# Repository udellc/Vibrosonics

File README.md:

# Vibrosonics

## Experience audio through vibration

**Vibrosonics** is a real-time audio-to-haptics system with an interactive web interface that allows deaf, hard-of-hearing, and sensory-focused users feel sound through vibrarions.

[**Documentation (Doxygen)**](https://udellc.github.io/Vibrosonics/) \
**Hardware:** Adafruit ESP32 Feather, MAX9744 Amplifier board, TT25-8 puck
transducer, 3.5mm audio jack cable \
**Dependencies:** [AudioLab](https://github.com/synytsim/AudioLab)
· [AudioPrism](https://github.com/udellc/AudioPrism)
· [Fast4ier](https://github.com/jmerc77/Fast4ier)

## Table of Contents

- [Why Vibrosonics Matters](#why-vibrosonics-matters)
- [Key Features](#key-features)
- [Arduino Setup](#arduino-setup)
- [Web Development Setup](#web-development-setup)
- [ESP32 Web Server Setup](#esp32-web-server-setup)
- [Developer Notes](#developer-notes)
- [Contributors](#contributors)

## Why Vibrosonics Matters

Millions of people experience barriers when it comes to audio-based media such as music, games, alerts, or live events. Vibrosoncis transforms those experiences by converting sound into meaningful tactile feedback.

Instead of hearing a beat, you **feel it**.

Built in collaboration with **[Cymaspace](https://www.cymaspace.org/)**, an organization whose goal is to make culture and arts accessible for the deaf and hard-of-hearing community, Vibrosonics is designed to make music, entertainment, and environments more inclusive while also opening up new immersive experiences for everyone. This group makes up our primary audience, as haptic feedback can be used to replace or enhance audio. Some secondary users would be employers whose work environments make pure audio based communication difficult. They could instead receive important audio cues through haptics.

## Key Features

**Real-Time Audio Conversion**
Transforms live audio input directly into haptic vibration with minimal latency.

**Configurable Settings Through Web Application**
A browser-based app allows users to adjust haptic feedback in real-time with no recompiling or device flashing required.

**Frequency-Aware Feedback**
Different pitches and intensities map to distinct vibration patterns, preserving musical structure and adding depth.

**Accessible by Design**
Built specifically for deaf and hard-of-hearing users, while also enhancing experiences for others.

_[View the most stable version on GitHub](https://github.com/udellc/Vibrosonics/tree/main)_

## Arduino Setup

### 1. Install Arduino IDE and ESP32 Board Support

- Download [Arduino IDE](https://www.arduino.cc/en/software/)
- Go to **Tools > Boards > Boards Manager**
- Search and install `esp32` by **Espressif Systems**

### 2. Set Board and Ports

- Plug in the board (you may need to install USB drivers)
- Go to the top drop down menu and click `Select other board and port...`
- In the pop up window, search for `Adafruit ESP32 Feather` and select it along
with `COMX` for port where `X` is a number 0-6
  - You may need to download a driver to see the port ([Windows
    Tutorial](https://randomnerdtutorials.com/install-esp32-esp8266-usb-drivers-cp210x-windows/))
  - On Linux, this is the `ch341` driver

### 3. Add Libraries

Navigate to the Arduino libraries folder. This is usually located in
`Documents/Arduino/libraries/` for Windows and `~/Arduino/libraries/` for Mac and Linux.

Clone the repositories into the libraries folder:

```bash
cd "/path/to/Arduino/libraries/"
git clone https://github.com/synytsim/AudioLab.git
git clone https://github.com/udellc/AudioPrism.git
git clone https://github.com/jmerc77/Fast4ier.git
```

Verify that the libraries are installed by opening Arduino IDE and going to
**Sketch > Include Library > Manage Libraries...**. You should see `AudioLab`,
`AudioPrism`, and `Fast4ier` in the list.

### 4. Upload a Sketch

You should be ready to use the example sketches or create your own! To upload a
sketch to the Vibrosonics hardware:

- Plug in the ESP32 via USB
- Open your own sketch or one of our examples from **File > Examples >
Vibrosonics > \[Example Name]**
- Press the upload (➜) in the top left to compile and upload your sketch

## Web Development Setup

### 1. Install Node.js and npm

- Download and install Node.js through your prefered web browser. This will also install npm.

### 2. Install Dependencies

- Open a terminal and navigate to the `WebApp/` directory of the repository.

- Run the following command to install the required dependencies:

```bash
npm install
```

### 3. Start the Development Server

- Run the following command to start the development server:

```bash
# This will start the server and provide a local URL at localhost. Once the server is running,
npm run dev

# Opens the application in your default web browser.
o

# Manually restarts the server
r

# Stops the server
q
```

### 4. Additional Commands

**Production Build:**
To build the application for production, run:

```bash
# This will produce optimized files in the `dist/` directory
npm run build

# This will preview the production build locally
npm run preview
```

**Run Linter Tool:**
To run ESLint for .js and .jsx files, run:

```bash
# This will scan the target files for any syntax issues or potential bugs
npm run lint

# This will automatically fix any fixable issues found by ESLint
npm run lint.fix
```

### 5. Troubleshooting

If you encounter any issues during setup or development, consider the following steps:

- Ensure that Node.js and npm are correctly installed by running `node -v` and `npm -v` in your terminal.
- Check for any error messages in the terminal and refer to the documentation of the specific tools or libraries being used.
- Make sure all dependencies are installed correctly by running `npm ci` for a clean install. If issues still persist, try deleting the `node_modules/` directory and running `npm install` again.

## ESP32 Web Server Setup

**SD File System Setup:**
To deploy the WiFi web app onto the ESP32, we'll need to store the web app onto a micro SD card connected to the ESP32. View `WebApp/main/fileSys.h` for the pin connections, these directions assume that the pins are connected properly.

**Note:** Uploading the web app onto the SD card only needs to be done everytime a new build of the web app is needed.

### 1. Setup Upload Mode (Necessary if web app is not on the ESP32, otherwise skip)

- Navigate to the `WebApp/main/config.h` file and uncomment the following line to setup the ESP32 in upload mode

```cpp
#define DEV_MODE_EN
```

- Build and upload `main.ino` in the ArduinoIDE once connected to a COM port.
- Connect to the Wi-Fi access point on your device, name of the network is **Vibrosonics-Dev**.
- Open a web browser and open `http://vibrosonics/dev`.
- Enter the directory you want to write to and select the file to upload.
- Click the upload button to write the file. **Note:** Open the Serial monitor in ArduinoIDE to view the files on the SD card.
- Once successful, exit the web app, comment out the `DEV_MODE_EN` macro and rebuild and upload `main.ino`.

### 2. Connect to the Web App

- Connect to the Wi-Fi access point on your device, name of the network is **Vibrosonics-Unsecure**.
- Open a web browser and navigate to `http://vibrosonics`.
- Follow the directions provided by the web app

## Developer Notes

### Library Architecture

The Vibrosonics library aims to streamline three processes to enable
translating audio into the haptic range: audio signal processing, audio
analysis and finally audio synthesis. We utilize a few libraries to achieve
this.

The first is AudioLab, which handles the audio signals between the external
hardware and the processor. It reads audio from the analog-to-digital
converters (ADC) and writes signals to the digital-to-analog converters (DAC)
for synthesis. The captured audio signals from the ADC are analyzed using the
other two library dependencies.

Fast4ier is used to perform the Fast Fourier Transform (FFT) on the signal
data, which converts it from a representation of the signal over time (time
domain) to a representation of how the signal is distributed over a range of
frequency bands (frequency domain). The bandwidth of the frequency domain, or
the max frequency, is equal to half of the sample rate of the ADC. Similarly,
the number of different frequency bands is equal to half of the window size of
the ADC.

AudioPrism is a library which analyzes the frequency domain data using various
algorithms. By filtering this data for different AudioPrism analysis modules,
we can detect certain elements of the audio signal. With music, this allows us
to detect percussion, isolate prominent vocals and melodies, and more. With
this analysis, distinct vibrations can be made to model elements of music by
re-synthesizing these findings through AudioLab translated down into the haptic
frequency range (0-230Hz).

### Web App Architecture

The VibroSonics application utilizes both cores on the ESP32 for efficient real-time audio processing and web-based configuration.

#### System Overview

- **Core 0**: Handles the web server and HTTP request processing
- **Core 1**: Runs the real-time audio analysis and haptic synthesis loop

#### Architecture Components

##### Frontend (Web App)

- **Framework**: React/Preact application built with Vite
- **Location**: Served from SD card on ESP32
- **Access**: Available at `http://vibrosonics` when connected to the device's WiFi AP
- **Pages**: 
  - Landing page for global settings
  - Network configuration page
  - Analysis modules configuration page
- **Communication**: Makes HTTP API calls to the ESP32 web server

##### Backend (ESP32 Web Server)

- **Server**: WebServer library running on Core 0
- **Endpoints**: RESTful API for configuration and real-time updates
- **Key Functions**:
  - `/network/*`: WiFi network scanning and connection
  - `/analysis/*`: Audio analysis configuration management
  - File serving for static web assets
- **Rate Limiting**: 500ms minimum interval for real-time setting updates

##### Inter-Core Communication

- **Mechanism**: Thread-safe message queue via `HapticSettings` singleton
- **Flow**:
  1. Web app sends HTTP request to ESP32 server
  2. Server parses request and creates `QueueMessage`
  3. Message added to queue in `HapticSettings`
  4. Audio loop (Core 1) checks for pending messages
  5. Messages processed to update `AnalysisConfig`
  6. Configuration changes applied to audio processing pipeline

##### Audio Analysis Loop (Core 1)

- **Real-time Processing**: Continuous audio input → analysis → haptic output
- **Configuration**: Uses shared `AnalysisConfig` updated via message queue
- **Modules**: Dynamic analysis modules (percussion detection, frequency analysis, etc.)
- **Synthesis**: Generates haptic feedback through AudioLab library

#### Data Flow

```
Web App (Browser) → HTTP Request → Web Server (Core 0) → Message Queue → Audio Loop (Core 1) → Haptic Output
```

#### Key Design Decisions

- **Dual-Core Utilization**: Separates web serving from real-time audio processing for reliability
- **Message Queue**: Thread-safe communication between cores without blocking
- **SD Card Storage**: Web app files stored on SD card for easy updates
- **Rate Limiting**: Prevents web interface from overwhelming the audio processing
- **Atomic Configuration Updates**: Ensures consistent state during real-time processing

### API Classes

- `VibrosonicsAPI`: This is the core class; it is a unified interface for audio
processing, analysis and synthesis
- `Grain`, `GrainList`, and `GrainNode`: These are the components for granular
synthesis. `Grain` is the main grain class, and the list and node classes provide a
way to manage a linked list of grains.

## Examples

We have an `examples` folder which contains individual programs that each
showcase a different feature or technique possible using Vibrosonics and
AudioPrism.

- Start with the `Template` example to see basic use of the API and for a
starting point for your own program.
- The `Grains` example demonstrates using the provided classes for granular
synthesis with a frequency and amplitude sweep, duration changes and wave shape
variations.
- `Percussion` showcases our current percussion detection method, which uses a
specially filtered frequency domain representation as input for an AudioPrism
percussion module. It utilizes grains to create haptic feedback corresponding
to the detected percussive hits.
- `Melody` is a similar example of strategic frequency domain processing, but
to bring out melodic elements of music. These elements are resynthesized by
translating the most prominent frequency peaks into the haptic range.
- `Vibrosonics` is our example demonstrating a combination of multiple
techniques (`Percussion` and `Melody`) to provide a real-time translation of
music to tactile feedback. Look here for an in-depth example utilizing the full
capabilities of our library.

## Contributors

### 2025-26 Software Team

- [Ivan Wong](https://github.com/IvanW5X)
- [Danielle Chang](https://github.com/danichang1)
- [Bella Mann](https://github.com/mannbella)
- [Ally Aoki](https://github.com/aokiam)

### 2024-25 Software Team

- [Walt Bringenberg](https://github.com/wwaltb)
- [Ben Kahl](https://github.com/ben-kahl)
- [Keith Reinhardt](https://github.com/reinhake)
- [Ashton Tilton](https://github.com/amputee20000)
- [Julia Yang](https://github.com/jjuliayang)

[LinkedIn Pages](https://dot.cards/vibrosonicscs)

### Special Thanks

- Dr. Chet Udell (Project leader and manager)
- Nick Synytsia (Developed AudioLab and advised software development for 2024-25)
- Alex Synytsia (Participated in hardware development during 2022-23)
- Vincent Vaughn (Advised software and hardware development)
- Hans Bestel (Project manager for software and hardware development during 2025-26)

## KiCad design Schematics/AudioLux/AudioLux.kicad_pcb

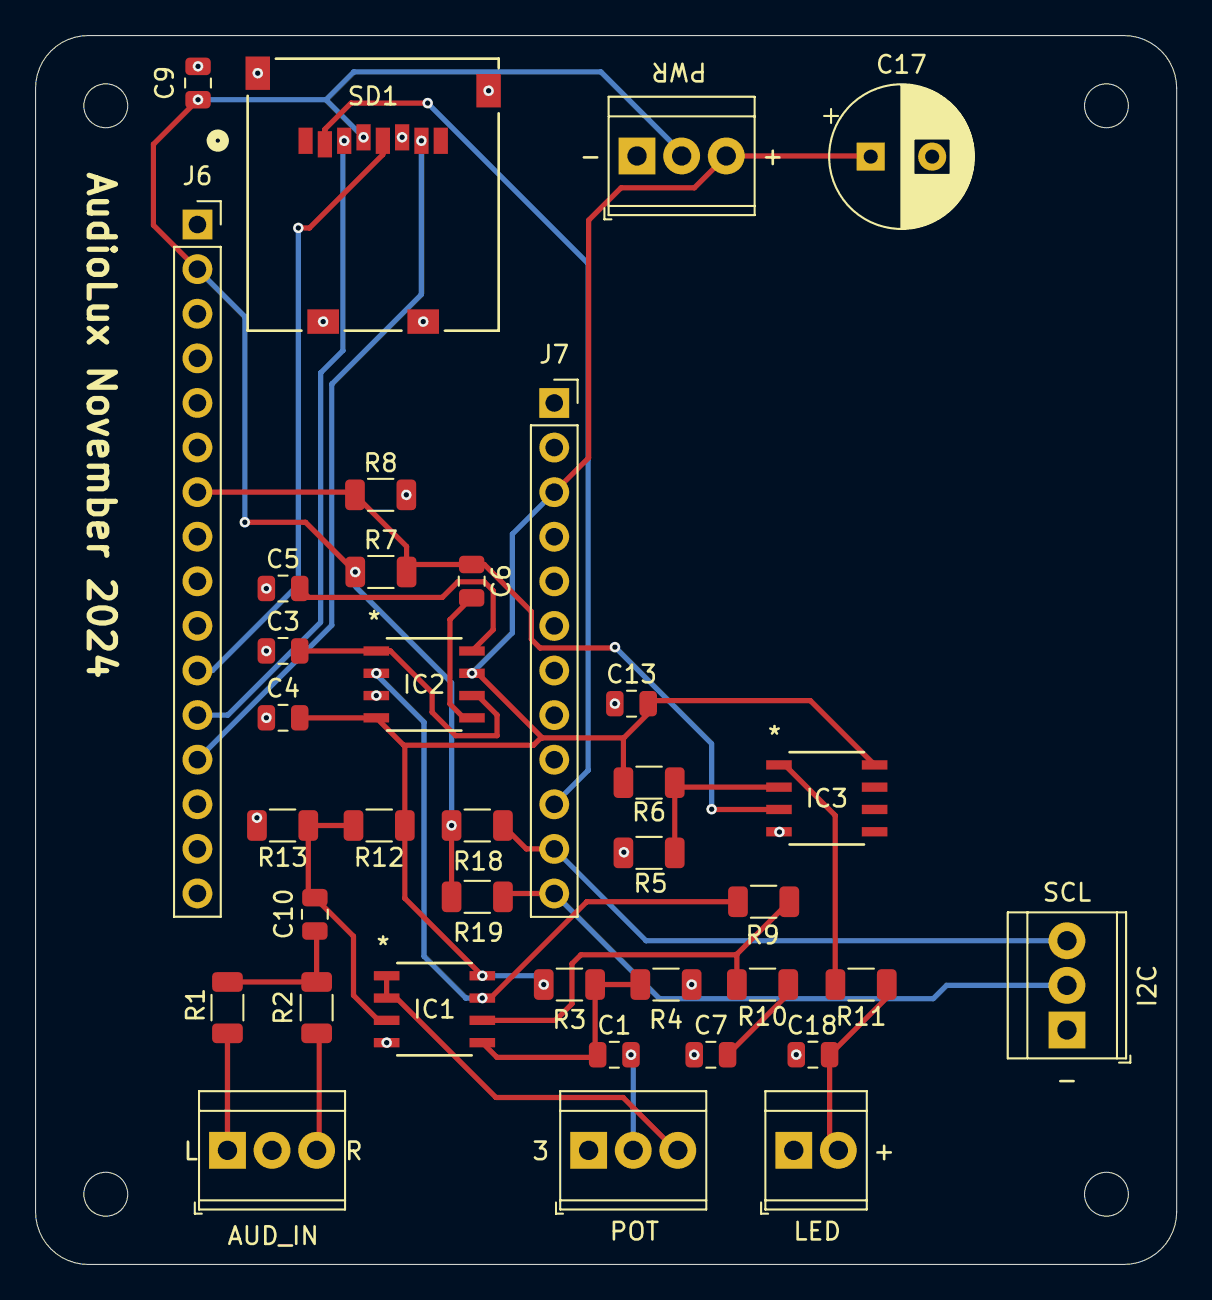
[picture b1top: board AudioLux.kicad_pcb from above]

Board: 2 copper layers, 65.0 x 70.0 mm, 37 parts (0 on the bottom side), 26 nets.

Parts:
C1, C6, C7, C10: 10uF; C_0805_2012Metric
C3, C4, C13, C18: 0.1uF; C_0805_2012Metric
C5: 100pF; C_0805_2012Metric
C9: 100nF; C_0805_2012Metric
C17: C_Polarized; CP_Radial_D8.0mm_P3.50mm
I2C: Screw_Terminal_01x03; TerminalBlock_TE_282834-3_1x03_P2.54mm_Horizontal
IC1, IC3: LMV358IDR; 21-0041B_8_MXM
IC2: MAX7403CSA+; 21-0041B_8_MXM
J1, J3, J4: Screw_Terminal_01x03; TerminalBlock_TE_282834-3_1x03_P2.54mm_Horizontal
J5: Screw_Terminal_01x02; TerminalBlock_TE_282834-2_1x02_P2.54mm_Horizontal
J6: Conn_01x16_Socket; PinSocket_1x16_P2.54mm_Vertical
J7: Conn_01x12_Socket; PinSocket_1x12_P2.54mm_Vertical
R1, R2, R3, R4, R7, R8, R12, R13, R18, R19: 10k; R_1206_3216Metric
R5: 7.5k; R_1206_3216Metric
R6: 5k; R_1206_3216Metric
R9: 22k; R_1206_3216Metric
R10: 6.2k; R_1206_3216Metric
R11: 150; R_1206_3216Metric
SD1: CONN_1660_ADA

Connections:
3V3: C9.2, J1.2, J6.2, R7.1, R18.2, R19.2, SD1.4 (VDD)
A2: C6.1, IC3.3 (1IN+), J6.7, R7.2, R8.1
GND: C3.1, C4.1, C5.1, C7.1, C9.1, C13.1, C17.2, C18.2, I2C.1, IC1.4 (GND), IC2.3 (GND), IC3.4 (GND), J1.1, J3.2, J4.1, J5.1, J6.4, R4.2, R5.2, R8.2, R13.2, SD1.6 (VSS), SD1.9, SD1.10, SD1.13, SD1.14
MI: J6.13, SD1.7 (DATA_OUT)
MO: J6.12, SD1.3 (DATA_IN)
unnamed: C7.2, R10.1
unnamed: C10.2, R1.1, R2.1
unnamed: C10.1, IC1.3 (1IN+), R12.2, R13.1
unnamed: IC1.1 (1OUT), IC1.2 (1IN-), J4.3
unnamed: C1.1, IC1.5 (2IN+), R3.2, R4.1
unnamed: IC1.6 (2IN-), R9.1, R10.2
unnamed: IC1.7 (2OUT), IC2.2 (IN), R9.2
unnamed: C5.2, IC2.8 (CLK)
unnamed: C3.2, IC2.1 (COM), IC2.6 (OS)
unnamed: C6.2, IC2.5 (OUT)
unnamed: IC3.2 (1IN-), R5.1, R6.2
unnamed: IC3.1 (1OUT), R11.2
unnamed: J3.1, R1.2
unnamed: J3.3, R2.2
unnamed: C1.2, J4.2
unnamed: C18.1, J5.2, R11.1
SCK: J6.11, SD1.5 (SCLK)
SCL: I2C.3, J7.11, R18.1
SDA: I2C.2, J7.12, R19.1
SD_CS: J7.10, SD1.2 (CS)
USB: C4.2, C13.2, C17.1, IC1.8 (VCC+), IC2.4 (VDD), IC2.7 (*SHDN), IC3.8 (VCC+), J1.3, J7.3, R3.1, R6.1, R12.1

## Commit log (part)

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2025-06-03 MapFrequency functions updates and Melody fixes
2025-06-03 deploy: be4e638036a2dff0ec68f6ccebaece9ec20628ce
2025-06-05 WIP: FM Integration
2025-10-27 Remove audioLabInputBuffer, directly pass vData buffer into AudioLab.ready()
2025-10-30 feat: rename VS web app directory to WebApp
2025-10-30 feat/modify web app lint yaml file
2025-10-31 refactor: Added devnotes, setup, and contributing docs. Refactored existing docs
2025-10-31 Update Doxygenfile inputs
2025-10-31 docs: Add formatting updates and set updated links for Git pages
2025-10-31 docs: Add code of conduct and formatting changes
2025-10-31 deploy: 31a71360c909d0df19c8af65c39eecaeb6edc35a
2025-10-31 deploy: 35f30a0e2704153544765ed94494baf933d6a018
2025-10-31 deploy: c6f5a74b4d8934179bfb75b0178c0904cb717b19
2025-10-31 deploy: 608fb7558ae11762c8beb31005699c3d9aa7edbc
2025-10-31 deploy: 08688217a906cf2047b15e068da13a9d47eca109
2025-10-31 docs: add table of contents
2025-10-31 docs: doc generation stable and updated git pages to current, remove publish pages workflow for refactor/docs branch
2025-11-04 refactor: remove Preact preset code in web app
2025-11-06 feat: setup wifi connection for ESP32 into local network, sends a basic html file
2025-11-07 feat: init web server to use LittleFS to store preact build files
2025-11-07 doc: add section for setup with LittleFS
2025-11-07 doc: Add directions for getting web app onto ESP32
2025-11-08 deploy: 17516140fd1e5b1b32c5920ec5ff6138888c4eec
2025-11-14 feat: update mirrorMode2 for testing
2025-11-18 add: setup initial web architecture
2025-11-18 add: add header and footer for the web app
2025-11-18 refactor: moved the header and footer component into their own files under components
2025-11-20 feat: ESP32 now runs as an access point for it's own network, and minor refactoring done
2025-11-20 refactor: clean up landing page
2025-11-20 feat: fix caching issues with web app runner environment
2025-11-20 fix: resolve issues with undefined references from libraries
2025-11-22 feat: update melody, mirrormode2, percussion examples
2025-11-22 feat: pass in window size to spectral tools functions in Vibrosonics.ino
2025-11-22 add: added routes to the network and modules page
2025-11-22 feat: minor styling to make slider vertical
2025-11-22 fix: minor styling and removed unecessary css import
2025-11-23 feat: implemented a working, mini file system with the SD card
2025-11-23 add: added a basic API request helper for GET and POST http methods
2025-11-23 feat: started the upload and web app modes for the web server
2025-11-23 remove: got rid of the getFile function
2025-11-23 feat: added a hostname for the web page
2025-11-23 docs: update file header comment
2025-11-23 fix: resolve Unexpected String concat lint error
2025-11-24 fix: removed the temporary svg logo and setup the header for potential tabs
2025-11-24 feat: added a top border for the footer
2025-11-24 feat: added a network card component to display the different networks in the network page
2025-11-24 feat: started the network page. currently can display networks given a valid networks json array
2025-11-24 refactor: formating changes
2025-11-26 fix: updated the functionality for the sliders and knobs
2025-11-26 feat: add functionality to print files for upload mode
2025-11-26 docs: update function header comments, adding briefs and params usage
2025-11-26 fix: addressing comments ivan made in github
2025-11-27 fix: hot fix to the web app lint runner workflow
2025-11-27 refactor: use prettier formatting
2025-11-28 refactor: formatting updates
2025-11-28 feat: add a removeFile method using a File reference
2025-11-28 add: added axios dependency to make API requests
2025-11-29 fix: update backend hostname
2025-11-29 fix: fixed issue with scanned networks not displaying properly
2025-11-29 docs: update to upload mode instruction docs
2025-11-29 fix: resolved linting errors and warnings
2025-12-03 feat: add almost working network connection request. needs invalid credential handling and new timeout method (too long results in ESP32 time slicing error)
2025-12-06 update: add a TODO note for the web app architecture
2026-01-16 feat: resolved network connection timeout issue
2026-01-17 fix: remove SPI.h header file
2026-01-17 feat: add functionality to connect to selected network on system boot
2026-01-22 fix: update package vulnerabilities
2026-01-22 add: replaced testing code for sendNetworkConnectResponse with status and added sendNetworkSsid API
2026-01-28 update: updated web app packages
2026-01-28 refactor: moved writing Wifi settings to memory into it's own function
2026-02-03 refactor: change http request events to queue request
2026-02-03 feat: add print statement for too many requests
2026-02-05 refactor: moved API handlers to the processRequest function
2026-02-06 feat: add per-output config for majorpeaks
2026-02-08 refactor: Add debugging mode for Serial printing
2026-02-08 docs: add function header comment for webRunner()
2026-02-09 feat: allow for config changes while running
2026-02-10 fix: fleshing out module params ui functionality
2026-02-10 feat: update example configs, add clearOutputModules()
2026-02-11 fix: project title and setup title incrementation
2026-02-12 formatting: move Status_T enum to top of namespace
2026-02-12 update: replaced PATCH method with PUT and removed TODO comment
2026-02-12 fix: added macro DEBUG_BEGIN to expand to nothing when debug disabled
2026-02-13 feat: rename outputconfig to moduleconfig, make base class uninstantiatable
2026-02-15 chore: add comments on config values
2026-02-16 cleanup: fix typos
2026-02-17 add: created HapticSettings singleton class with testing functions
2026-02-18 fix: fixed issue with uploading web app files from fresh SD card
2026-02-18 feat: added a global context for the audio settings data which all components can modify
2026-02-19 feat: updated base module fields to use more details
2026-02-19 add: started adding (not yet implemented) functions for the singleton haptic settings
2026-02-19 fix: added missing arg for debugging print
2026-02-19 add: started updateHaptic API endpoint
2026-02-19 remove: removed unused callback for sliderChanged
2026-02-20 add: added onSubmit handler from feat/configurableAPI branch
2026-02-20 feat: added atomic functions for loading and writing new config settings
2026-02-20 add: added starter code for mapping analysis modules
2026-02-20 feat: added back assignOutputModules test from feat/configurableAPI branch
2026-02-20 fix: fixed typo
2026-02-20 edit: change web server delay back 10 100ms
2026-02-20 edit: modified json structures, using one for display and one for pure data
2026-02-21 add: added type field
2026-02-21 edit: changed new MajorPeaks to unique pointers
2026-02-21 fix: revert major peaks setup back to 1 peak
2026-02-21 add: added helper factory for making modules based on type and added safe values for global settings
2026-02-22 add: added helpers for packaging haptic settings into JSON structure
2026-02-22 feat: added persistant data in frontend for global and modules data
2026-02-22 feat: added adjustable UI component for global data
2026-02-22 edit: made first enum numbers 0
2026-02-22 feat: updated config settings for audio analysis API endpoints
2026-02-22 feat: added adjustable audio analysis for global settings
2026-02-22 edit: modified json structures to match backend and for UI descriptions/restrictions
2026-02-22 remove: deleted old json structure placeholders
2026-02-22 add: added early return for HTTP_OPTIONS method
2026-02-22 add: added on change handler for page navigation. for future header changes
2026-02-22 ui: UI display changes for fixed heights on major components
2026-02-23 feat: add percussion to configurable sketch
2026-02-23 feat: added a atomic dirty bool for assigning new modules to the module group
2026-02-23 fix: updated max frequency
2026-02-23 feat: add button to print ESP memory available
2026-02-23 ui: minor UI changes
2026-02-24 cleanup: adding comments and minor changes
2026-02-24 feat: rebuild percussion modules, add amplitude ducking
2026-02-24 edit: moved ModulePtr alias to storage.h
2026-02-24 refactor: remove hasPercussion param from synthesizePeak
2026-02-24 format: use prettier formatting
2026-02-24 edit: replace custom output channel dropbox with built in select component
2026-02-27 temp: added example configs for UI testing
2026-02-27 feat: moved text entry input to knob component
2026-02-27 refactor: removed text entry and moved to knob component
2026-02-27 remove: removed temp data json files
2026-02-27 feat: made analysis module component dynamic for major peaks and percussion modules
2026-02-27 docs: added header comments and other minor changes
2026-03-02 resolve: added more comments to the code i added
2026-03-09 feat: move minAmpNorm into global settings
2026-03-10 feat: delete modules
2026-03-10 feat: added nav bar and got rid of line
2026-03-10 feat: added infoButton functionality
2026-03-10 feat: added rock and jazz presets to webapp
2026-03-11 feat: integrated add/delete modules with real time updates
2026-03-12 feat: cleaning up modules page
2026-03-12 feat: added logo and external linking functionality
2026-03-12 feat: changed font
2026-03-12 feat: added 'add module' functionality but will need to test later
2026-03-12 deploy: 6cffbf4b6ae33a0c7c56a1469ed10b59e2bcc6c8
2026-03-13 fix: cosmetic changes and library saving work
2026-04-17 fix: fixed network page ui to look like rest of webapp
2026-04-17 refactor: clean up of audio analysis functions
2026-04-17 fix: swap SD pin from 16 to 21
2026-04-22 fix: added more functionality to the info popups
2026-04-22 fix: small tweak to radio page
2026-04-23 fix: updating modules page to allign with figma designs
2026-04-26 fix: fix vibrosonics include
2026-04-26 deploy: e4f991dbf9762d9541ece1ab3773d5af09e09cd4
2026-04-26 adjusted image sizes
2026-04-26 fixed image formatting again
2026-04-26 updated spectrogram image
2026-04-27 updated Hans' description
2026-04-27 feat: add modules updates in real time
2026-04-27 cleanup: remove unused variable
2026-04-27 docs: comment updates
2026-04-30 feat: add comments to handleChangeModuleType
2026-05-01 fix: fixed static percussion bug
2026-05-01 cleaup: fixed and ignored some web app linting problems
2026-05-01 fix: small merge changes
2026-05-01 fix: load settings and clear current settings in the project library have been temp. fixed
2026-05-06 feat: add walkthrough starter code
2026-05-07 fix: cleaning up tutorial code
2026-05-08 feat: update minampnorm knob values
2026-05-15 fix: fix past merge issues, move minampnorm
2026-05-15 fix: add missing utils import
2026-05-15 fix: updated the functionality for the modules
2026-05-18 feat: test presets for A Tear in Space
2026-05-18 feat: added more descriptions to the info buttons and added more details to the walkthrough
2026-05-19 fix: move minampnorm to module level
2026-05-21 feat: tweak major peaks presets
2026-05-22 feat: update presets for different song
2026-05-24 add: added helper function for entering update loop for SD writes
2026-05-24 cleanup: remove unused file
2026-05-24 misc: update font to inter for on-device UI
2026-05-29 remove: delete unused file
2026-05-29 feat: added percussion presets for Strobe and Calabria 2008
2026-05-29 fix: addressing pr comments
2026-05-29 fix: revert Vibrosonics example
2026-05-29 fix: add placeholder code fot loadProject and fix lint errors
2026-05-29 feat: add bass & melody for calabria 2008 and strobe
2026-05-31 feat: added FM Radio contents to repo
2026-05-31 fix: re-add submitConfig API endpoint for presets
2026-06-03 chore: fixed README file extension
